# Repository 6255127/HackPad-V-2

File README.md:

# Hackpad

A small wireless macropad with 9 keys, a rotary encoder and an OLED screen. It works over Bluetooth or USB-C, and it runs off a little LiPo battery that charges through the same USB-C port.

## What's on it

- 9 keys in a 3x3 grid
- A rotary encoder (volume by default)
- 5 LEDs that show battery level while charging, go green when it's full, and blink blue when it isn't paired
- A 2.42" OLED
- Seeed XIAO nRF52840 as the brain, since it already has Bluetooth and battery charging built in

## The PCB

I picked the XIAO nRF52840 so I wouldn't have to build the Bluetooth and charging parts myself. I tried a bunch of layouts and kept the one with the smallest footprint.

## The case

It has a clear cover so you can see the LEDs. It's pretty thick, and that's because of the battery.

## Firmware

The firmware is basic, and AI helped write it. It sends keys over Bluetooth and USB, and drives the LEDs and screen.

## Status

Design is finished and I think it's ready to ship. The full build log is in [journal.md](journal.md).

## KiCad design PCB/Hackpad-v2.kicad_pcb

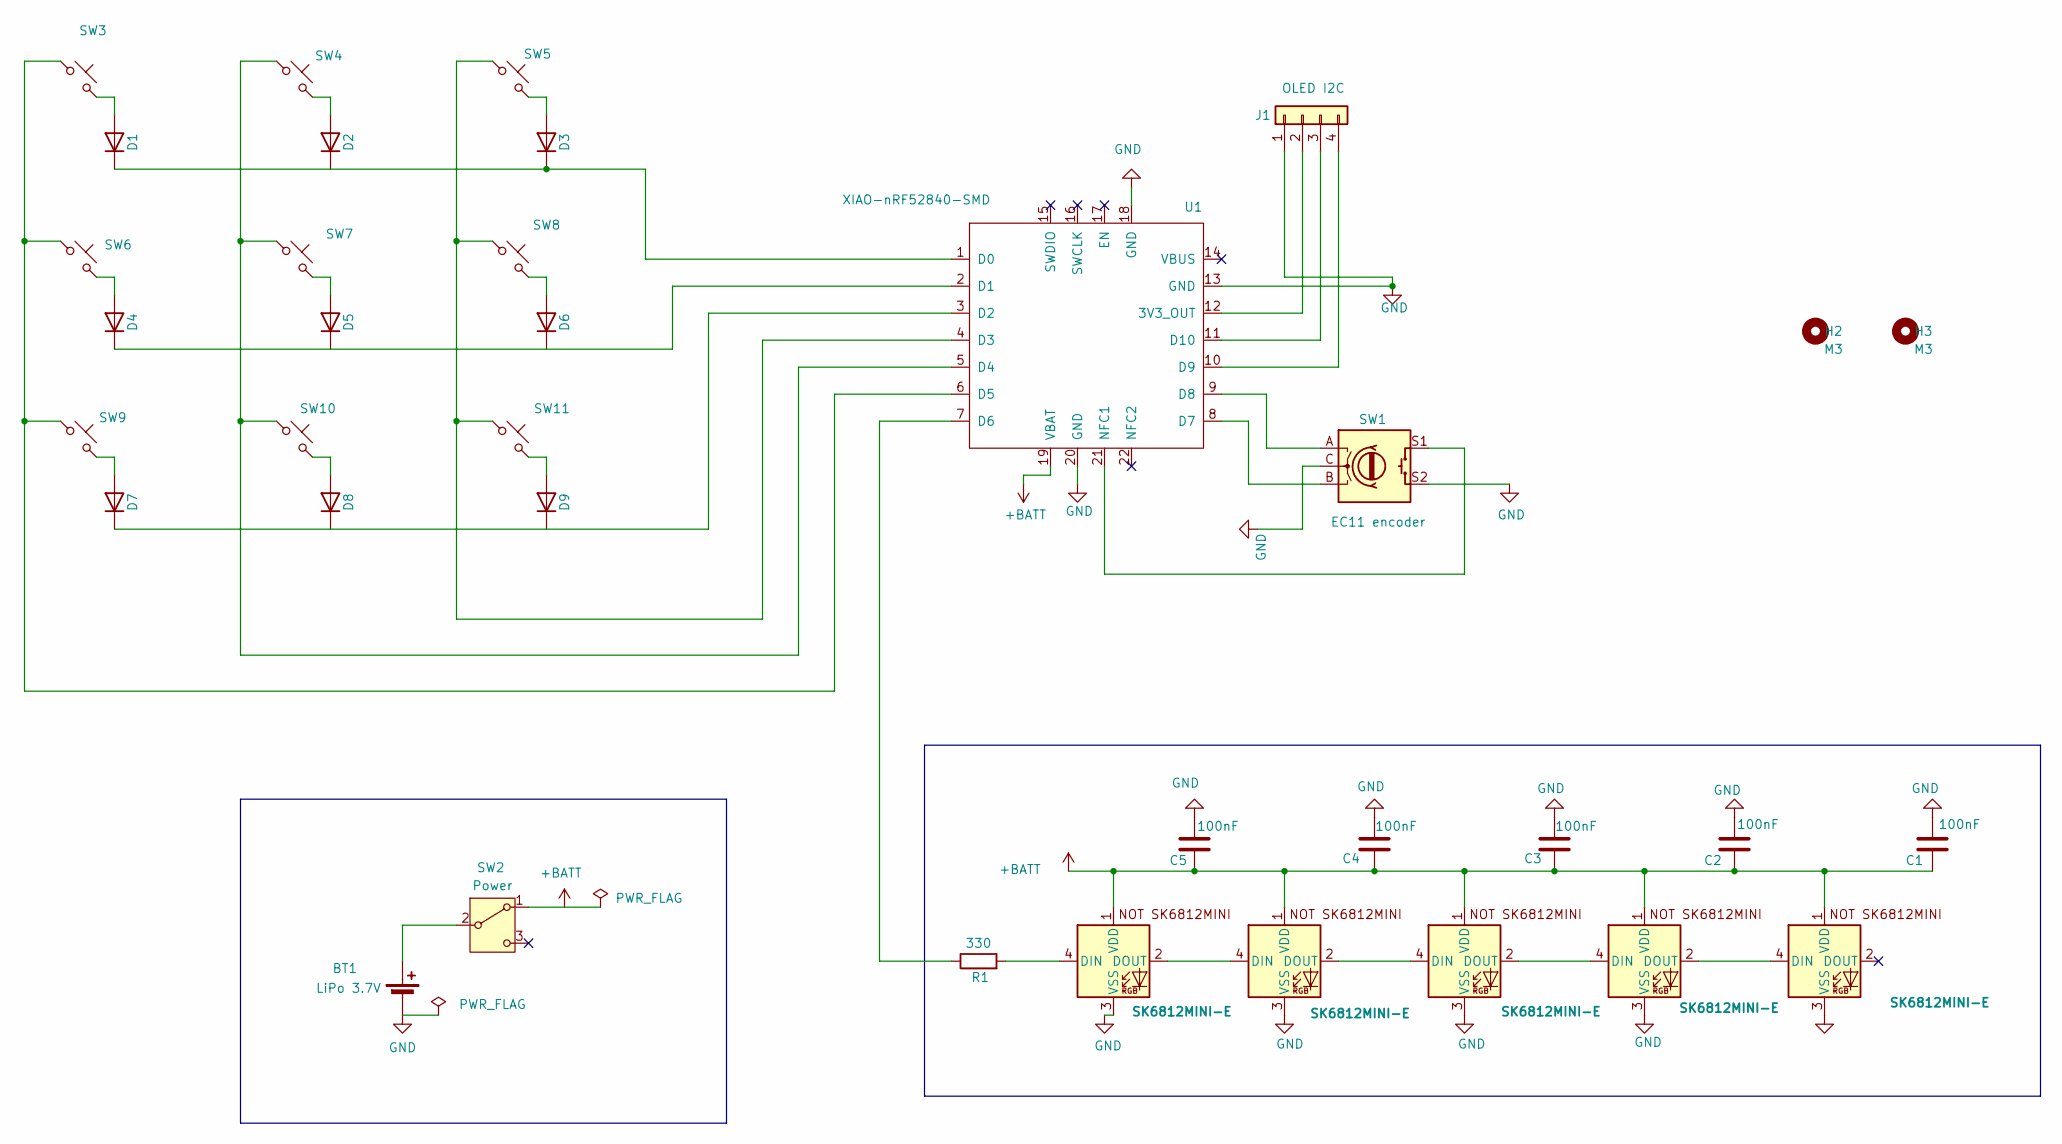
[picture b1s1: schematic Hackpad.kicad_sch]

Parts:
BT1: LiPo 3.7V; JST_PH_S2B-PH-K_1x02_P2.00mm_Horizontal
C1, C2, C3, C4, C5: 100nF; C_Disc_D5.0mm_W2.5mm_P5.00mm
D1, D2, D3, D4, D5, D6, D7, D8, D9: 1N4148; D_DO-35_SOD27_P7.62mm_Horizontal
D10, D11, D12, D13, D14: SK6812MINI-E; SK6812MINI-E_fixed
H2, H3: M3; MountingHole_3.2mm_M3
J1: OLED I2C; PinSocket_1x04_P2.54mm_Vertical
R1: 330; R_Axial_DIN0207_L6.3mm_D2.5mm_P7.62mm_Horizontal
SW1: EC11 encoder; RotaryEncoder_Alps_EC11E-Switch_Vertical_H20mm
SW2: Power; SW_Slide_SPDT_Angled_CK_OS102011MA1Q
SW3, SW4, SW5, SW6, SW7, SW8, SW9, SW10, SW11: MX key; SW_Cherry_MX_1.00u_PCB
U1: XIAO-nRF52840-SMD

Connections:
+BATT: C1.1, C2.1, C3.1, C4.1, C5.1, D10.1 (VDD), D11.1 (VDD), D12.1 (VDD), D13.1 (VDD), D14.1 (VDD), SW2.1 (A), U1.19 (VBAT)
GND: BT1.2 (-), C1.2, C2.2, C3.2, C4.2, C5.2, D10.3 (VSS), D11.3 (VSS), D12.3 (VSS), D13.3 (VSS), D14.3 (VSS), J1.1, SW1.C, SW1.S2, U1.13 (GND), U1.18 (GND), U1.20 (GND)
unnamed: BT1.1 (+), SW2.2 (B)
unnamed: D1.2 (A), SW3.2
unnamed: D1.1 (K), D2.1 (K), D3.1 (K), U1.1 (D0)
unnamed: D2.2 (A), SW4.2
unnamed: D3.2 (A), SW5.2
unnamed: D4.2 (A), SW6.2
unnamed: D4.1 (K), D5.1 (K), D6.1 (K), U1.2 (D1)
unnamed: D5.2 (A), SW7.2
unnamed: D6.2 (A), SW8.2
unnamed: D7.2 (A), SW9.2
unnamed: D7.1 (K), D8.1 (K), D9.1 (K), U1.3 (D2)
unnamed: D8.2 (A), SW10.2
unnamed: D9.2 (A), SW11.2
unnamed: D10.4 (DIN), R1.2
unnamed: D10.2 (DOUT), D11.4 (DIN)
unnamed: D11.2 (DOUT), D12.4 (DIN)
unnamed: D12.2 (DOUT), D13.4 (DIN)
unnamed: D13.2 (DOUT), D14.4 (DIN)
unnamed: J1.2, U1.12 (3V3_OUT)
unnamed: J1.3, U1.11 (D10)
unnamed: J1.4, U1.10 (D9)
unnamed: SW5.1, SW8.1, SW11.1, U1.4 (D3)
unnamed: SW4.1, SW7.1, SW10.1, U1.5 (D4)
unnamed: SW3.1, SW6.1, SW9.1, U1.6 (D5)
unnamed: R1.1, U1.7 (D6)
unnamed: SW1.B, U1.8 (D7)
unnamed: SW1.A, U1.9 (D8)
unnamed: SW1.S1, U1.21 (NFC1)

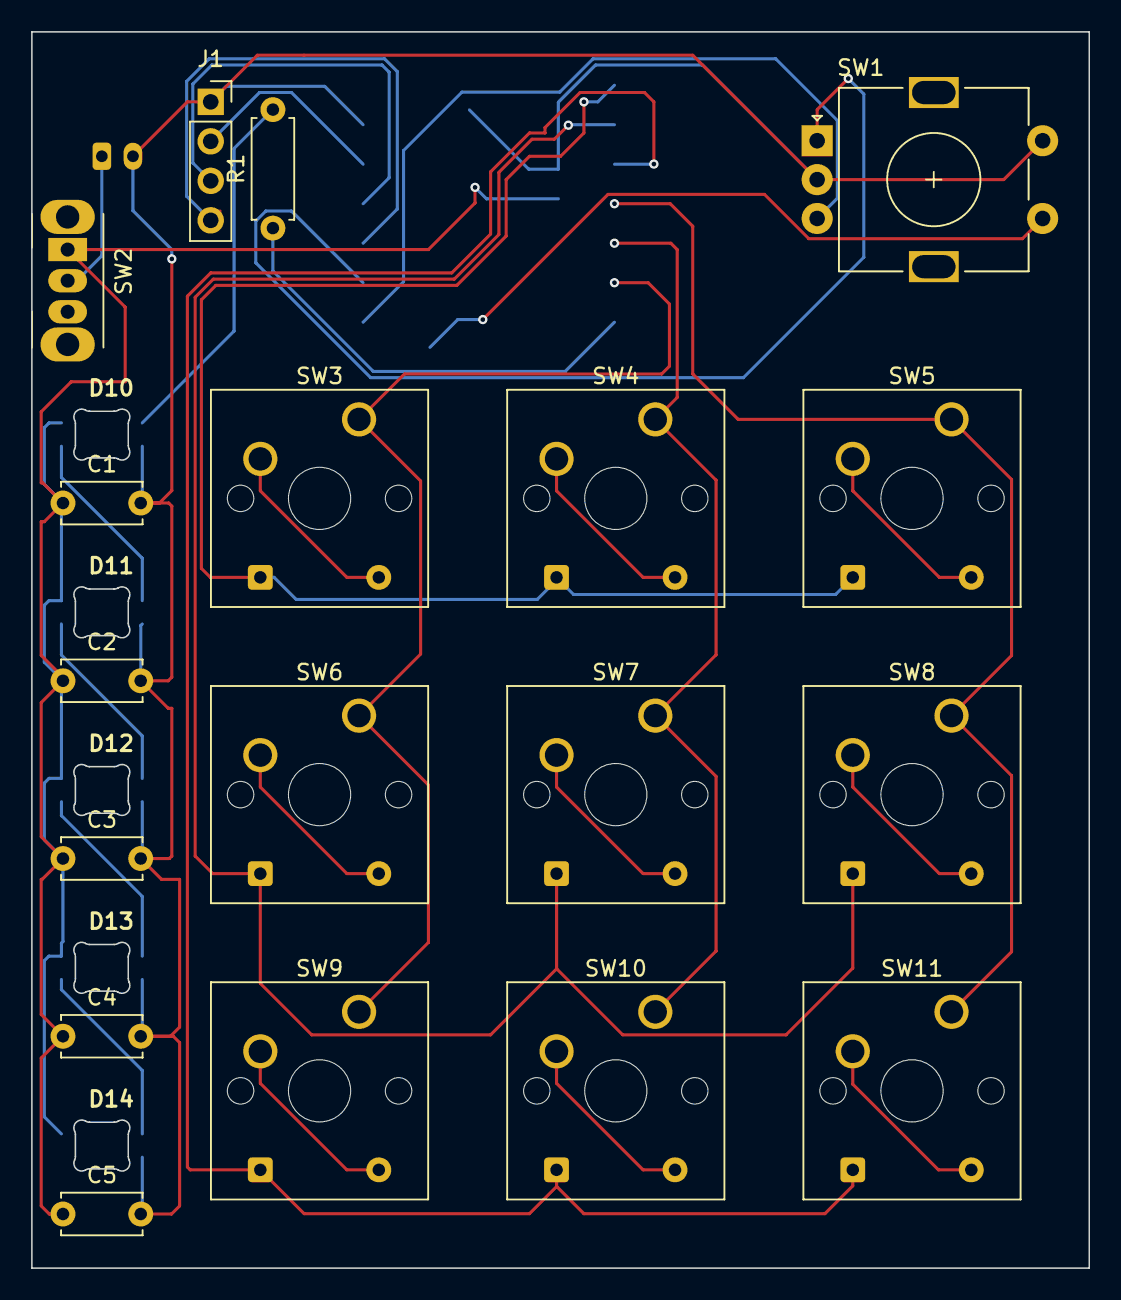
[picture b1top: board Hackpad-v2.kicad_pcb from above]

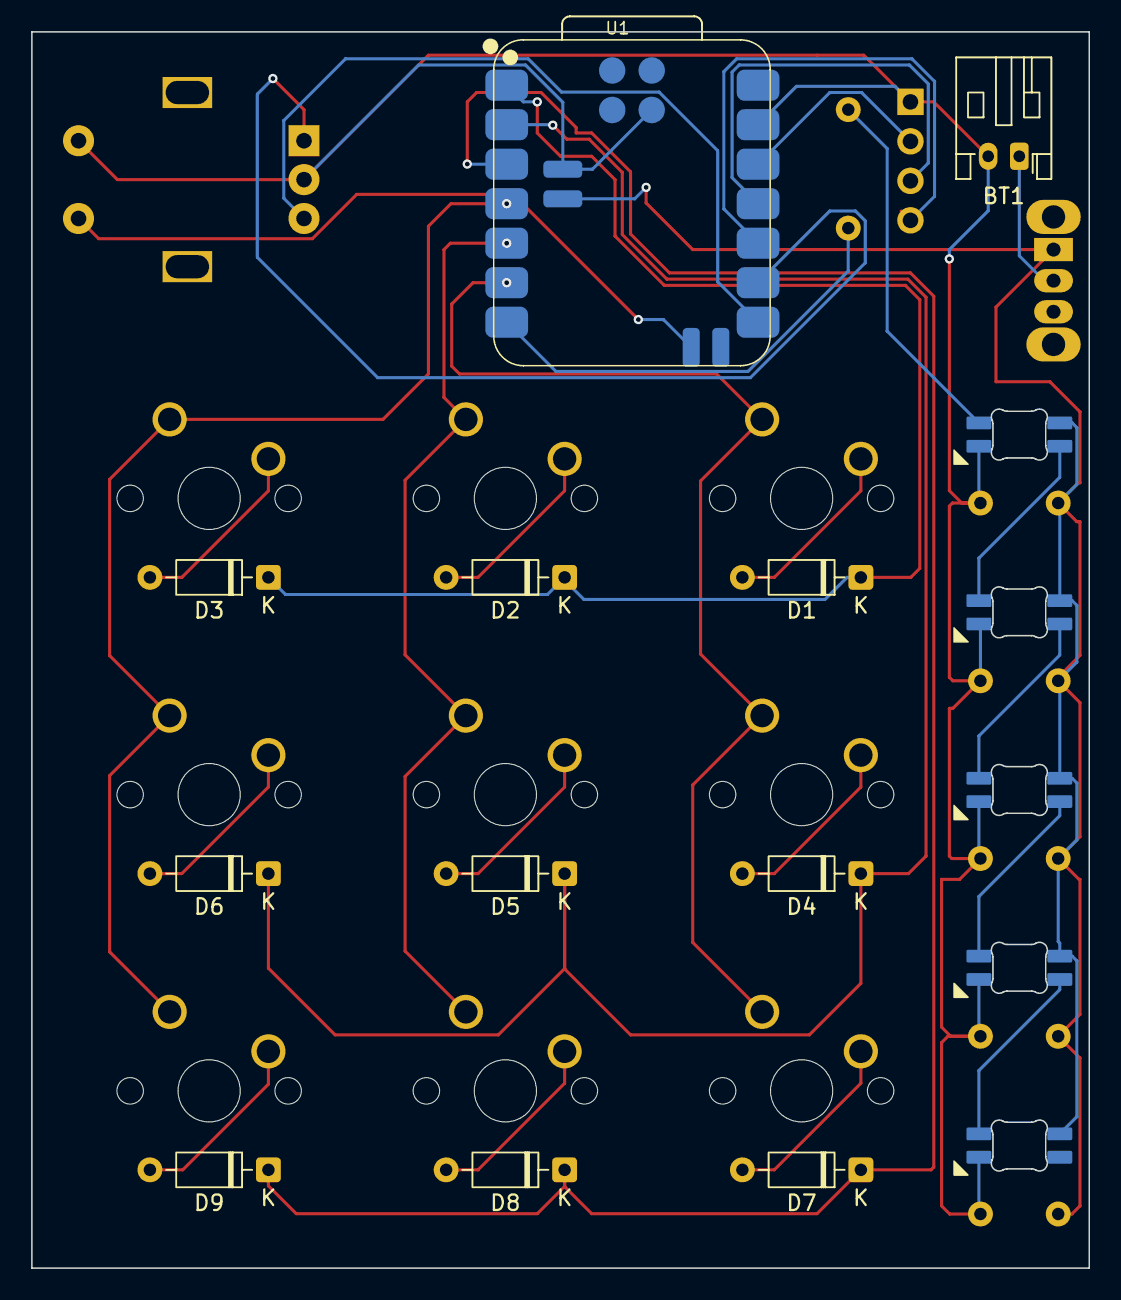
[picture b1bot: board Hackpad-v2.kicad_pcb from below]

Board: 2 copper layers, 68.0 x 79.5 mm, 34 parts (11 on the bottom side), 30 nets.
